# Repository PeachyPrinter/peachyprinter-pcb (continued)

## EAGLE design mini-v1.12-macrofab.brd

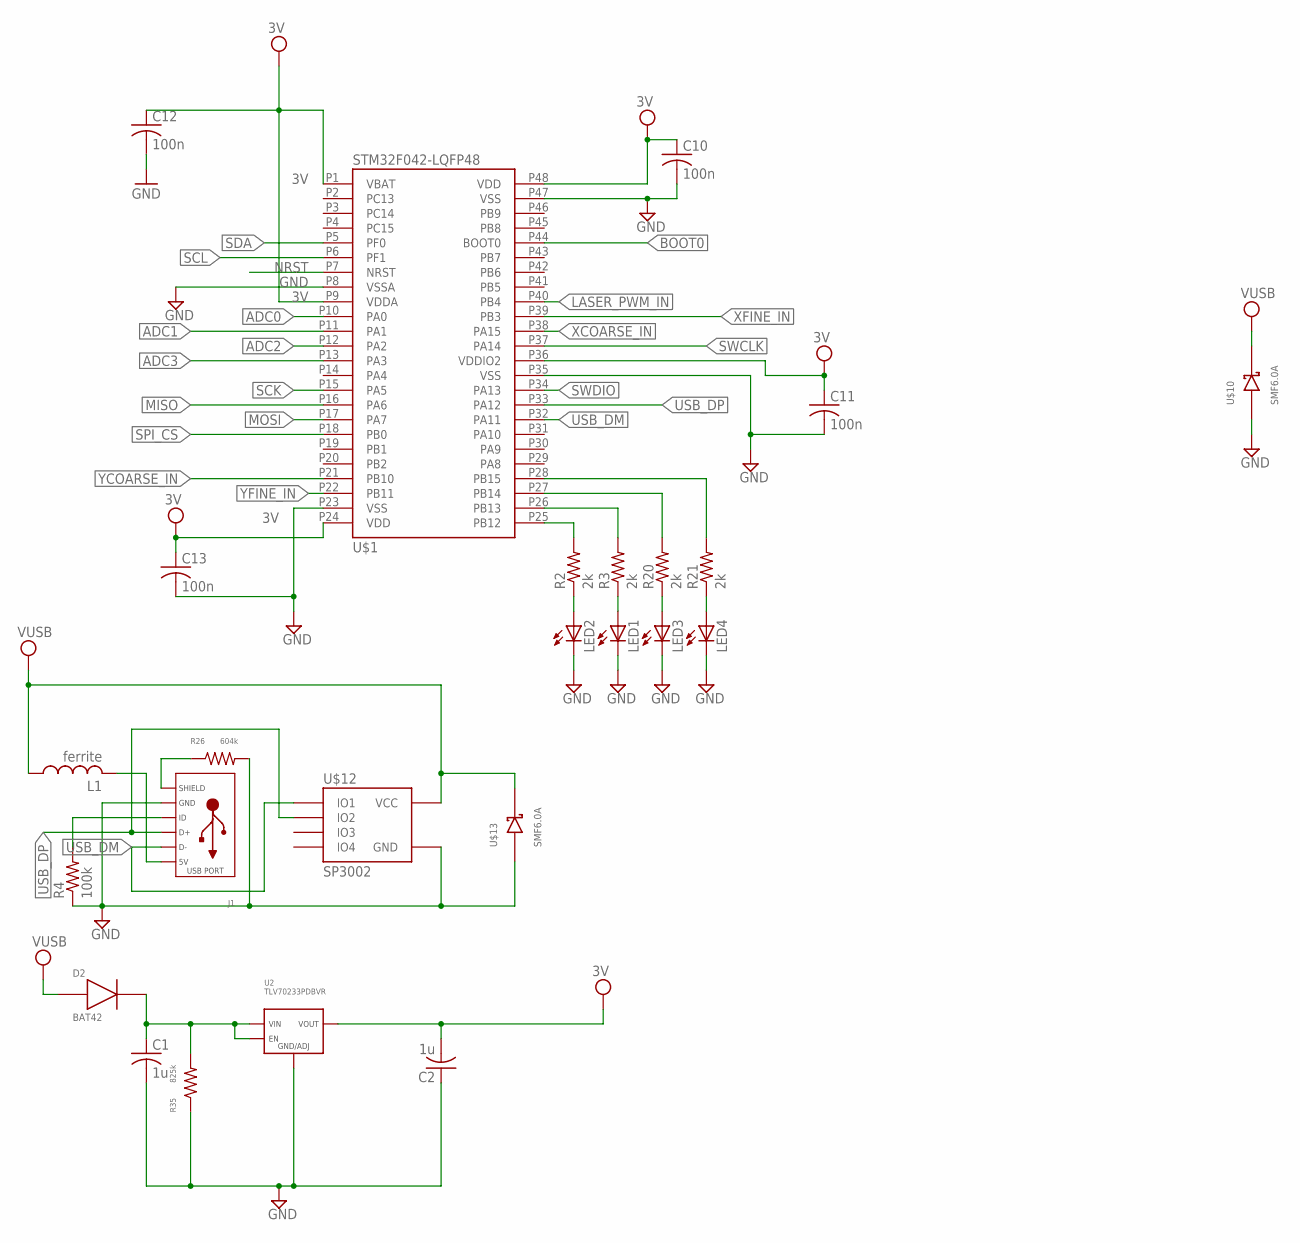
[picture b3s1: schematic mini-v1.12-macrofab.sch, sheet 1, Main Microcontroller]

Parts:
C1, C2: 1u; C0603
C10, C11, C12, C13: 100n; C0603
D2: BAT42; SOD323
J1: USB_MICRO_RIGHT; MICROUSB-RIGHT
L1: ferrite; C0603
LED1, LED2, LED3, LED4: LEDCHIP-LED0603; CHIP-LED0603
R2, R3, R20, R21: 2k; R0603
R4: 100k; R0603
R26: 604k; R0603
R35: 825k; R0603
U2: TLV70233PDBVR; SOT-23-5
U$1: STM32F042-LQFP48; LQFP48
U$10, U$13: SMF6.0A; SOD123
U$12: SP3002; SC70-6

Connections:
3V: C2.2, C10.1, C11.1, C12.1, C13.1, U2.P$5 (VOUT), U$1.P1 (VBAT), U$1.P9 (VDDA), U$1.P24 (VDD), U$1.P36 (VDDIO2), U$1.P48 (VDD); also elsewhere on the board
ADC0: U$1.P10 (PA0); also elsewhere on the board
ADC1: U$1.P11 (PA1); also elsewhere on the board
ADC2: U$1.P12 (PA2); also elsewhere on the board
ADC3: U$1.P13 (PA3); also elsewhere on the board
BOOT0: U$1.P44 (BOOT0); also elsewhere on the board
GND: C1.2, C2.1, C10.2, C11.2, C12.2, C13.2, J1.5 (GND), LED1.C, LED2.C, LED3.C, LED4.C, R4.1, R26.P$2, R35.P$1, U2.P$2 (GND/ADJ), U$1.P8 (VSSA), U$1.P23 (VSS), U$1.P35 (VSS), U$1.P47 (VSS), U$10.ANODE, U$12.P2 (GND), U$13.ANODE; also elsewhere on the board
LASER_PWM_IN: U$1.P40 (PB4); also elsewhere on the board
MISO: U$1.P16 (PA6); also elsewhere on the board
MOSI: U$1.P17 (PA7); also elsewhere on the board
unnamed: R2.2, U$1.P25 (PB12)
unnamed: LED2.A, R2.1
unnamed: C1.1, D2.1, R35.P$2, U2.P$1 (VIN), U2.P$3 (EN)
unnamed: J1.4 (ID), R4.2
unnamed: LED1.A, R3.1
unnamed: R3.2, U$1.P26 (PB13)
unnamed: J1.1 (5V), L1.2
unnamed: J1.S1 (SLD), J1.S2 (SLD), J1.S3 (SLD), J1.S4 (SLD), J1.S5 (SLD), J1.S6 (SLD), R26.P$1
unnamed: LED3.A, R20.1
unnamed: LED4.A, R21.1
unnamed: R20.2, U$1.P27 (PB14)
unnamed: R21.2, U$1.P28 (PB15)
NRST: U$1.P7 (NRST); also elsewhere on the board
SCK: U$1.P15 (PA5); also elsewhere on the board
SCL: U$1.P6 (PF1); also elsewhere on the board
SDA: U$1.P5 (PF0); also elsewhere on the board
SPI_CS: U$1.P18 (PB0); also elsewhere on the board
SWCLK: U$1.P37 (PA14); also elsewhere on the board
SWDIO: U$1.P34 (PA13); also elsewhere on the board
USB_DM: J1.2 (D-), U$1.P32 (PA11), U$12.P1 (IO1)
USB_DP: J1.3 (D+), U$1.P33 (PA12), U$12.P3 (IO2)
VUSB: D2.2, L1.1, U$10.CATHODE, U$12.P5 (VCC), U$13.CATHODE; also elsewhere on the board
XCOARSE_IN: U$1.P38 (PA15); also elsewhere on the board
XFINE_IN: U$1.P39 (PB3); also elsewhere on the board
YCOARSE_IN: U$1.P21 (PB10); also elsewhere on the board
YFINE_IN: U$1.P22 (PB11); also elsewhere on the board

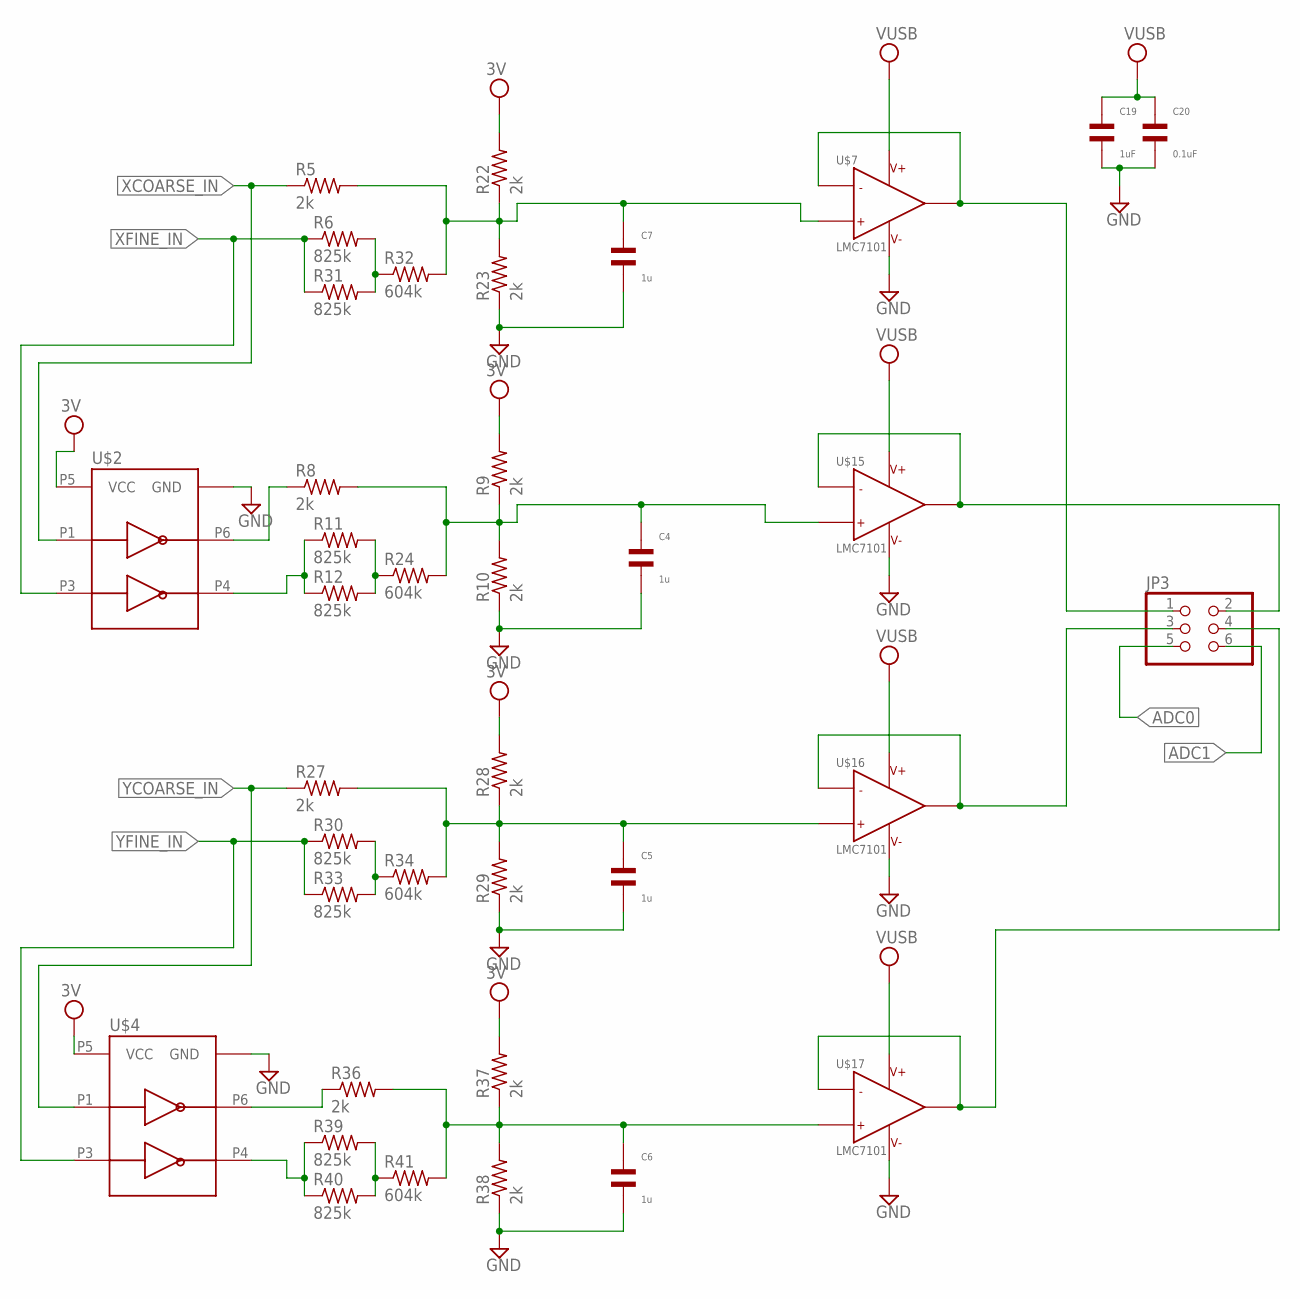
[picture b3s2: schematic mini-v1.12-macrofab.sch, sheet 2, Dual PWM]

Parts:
C4, C5, C6, C7: 1u; C0603
C19: 1uF; C0603
C20: 0.1uF; C0603
JP3: PINHD-2X3; 2X03
R5, R8, R9, R10, R22, R23, R27, R28, R29, R36, R37, R38: 2k; R0603
R6, R11, R12, R30, R31, R33, R39, R40: 825k; R0603
R24, R32, R34, R41: 604k; R0603
U$2, U$4: NC7WZ14P6X; SC70-6
U$7, U$15, U$16, U$17: LMC7101; SOT23-5

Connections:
3V: R9.2, R22.2, R28.2, R37.2, U$2.P5 (VCC), U$4.P5 (VCC); also elsewhere on the board
ADC0: JP3.5; also elsewhere on the board
ADC1: JP3.6; also elsewhere on the board
COARSE1: R8.1, U$2.P6 (Y1)
FINE1: R11.1, R12.1, U$2.P4 (Y2)
FINE3: R39.1, R40.1, U$4.P4 (Y2)
GND: C4.P$2, C5.P$2, C6.P$2, C7.P$2, C19.P$2, C20.P$2, R10.1, R23.1, R29.1, R38.1, U$2.P2 (GND), U$4.P2 (GND), U$7.5, U$15.5, U$16.5, U$17.5; also elsewhere on the board
unnamed: R36.1, U$4.P6 (Y1)
unnamed: R11.2, R12.2, R24.1
unnamed: C4.P$1, R8.2, R9.1, R10.2, R24.2, U$15.3
unnamed: R30.2, R33.2, R34.1
unnamed: R6.2, R31.2, R32.1
unnamed: C5.P$1, R27.2, R28.1, R29.2, R34.2, U$16.3
unnamed: R39.2, R40.2, R41.1
unnamed: C6.P$1, R36.2, R37.1, R38.2, R41.2, U$17.3
OUT: JP3.1, U$7.1, U$7.4
OUT1: JP3.2, U$15.1, U$15.4
OUT2: JP3.3, U$16.1, U$16.4
OUT3: JP3.4, U$17.1, U$17.4
VUSB: C19.P$1, C20.P$1, U$7.2, U$15.2, U$16.2, U$17.2; also elsewhere on the board
XCOARSE_IN: R5.1, U$2.P1 (A1); also elsewhere on the board
XFINE_IN: R6.1, R31.1, U$2.P3 (A2); also elsewhere on the board
XSUM: C7.P$1, R5.2, R22.1, R23.2, R32.2, U$7.3
YCOARSE_IN: R27.1, U$4.P1 (A1); also elsewhere on the board
YFINE_IN: R30.1, R33.1, U$4.P3 (A2); also elsewhere on the board

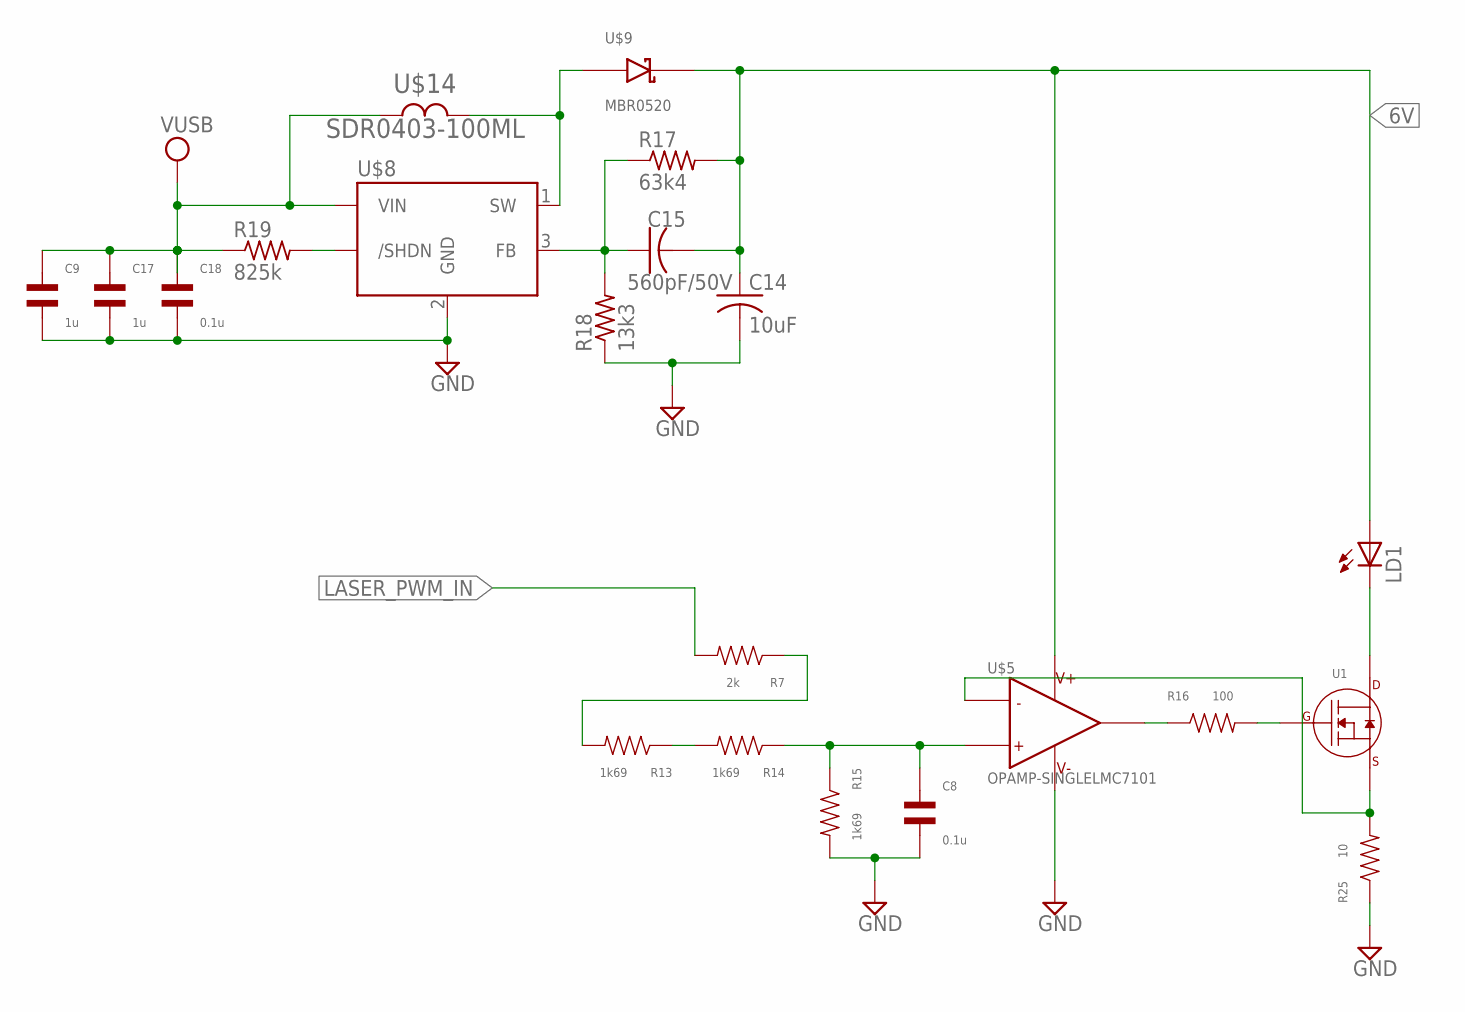
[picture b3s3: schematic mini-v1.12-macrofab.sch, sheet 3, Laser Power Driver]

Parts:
C8, C18: 0.1u; C0603
C9, C17: 1u; C0603
C14: 10uF; C0603
C15: 560pF/50V; C0603
LD1: LASERDIODELD2; LASERDIODE2; MPN 3 x (0552-2-15-15-11-27-10-0)
R7: 2k; R0603
R13, R14, R15: 1k69; R0603
R16: 100; R0603
R17: 63k4; R0603
R18: 13k3; R0603
R19: 825k; R0603
R25: 10; R0603
U1: N-CHANNEL_FET_SOT-23-3; SOT-23-3
U$5: OPAMP-SINGLELMC7101; SOT23-5
U$8: LMR62014; SOT23-5
U$9: MBR0520; SOD123
U$14: SDR0403-100ML; SDR0403

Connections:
6V: C14.1, C15.2, LD1.P$1 (A), R17.2, U$5.2 (V+), U$9.CATHODE
GND: C8.P$2, C9.P$2, C14.2, C17.P$2, C18.P$2, R15.P$2, R18.1, R25.P$1, U$5.5 (V-), U$8.2 (GND); also elsewhere on the board
LASER_PWM_IN: R7.P$2; also elsewhere on the board
unnamed: R7.P$1, R13.P$2
unnamed: R13.P$1, R14.P$2
unnamed: C8.P$1, R14.P$1, R15.P$1, U$5.3 (IN+)
unnamed: U$8.1 (SW), U$9.ANODE, U$14.P$2
unnamed: LD1.P$3 (C), U1.P$3 (DRAIN)
unnamed: R25.P$2, U1.P$2 (SOURCE), U$5.4 (IN-)
unnamed: R16.P$2, U1.P$1 (GATE)
unnamed: R16.P$1, U$5.1 (OUT)
unnamed: C15.1, R17.1, R18.2, U$8.3 (FB)
unnamed: R19.2, U$8.4 (/SHDN)
VUSB: C9.P$1, C17.P$1, C18.P$1, R19.1, U$8.5 (VIN), U$14.P$1; also elsewhere on the board

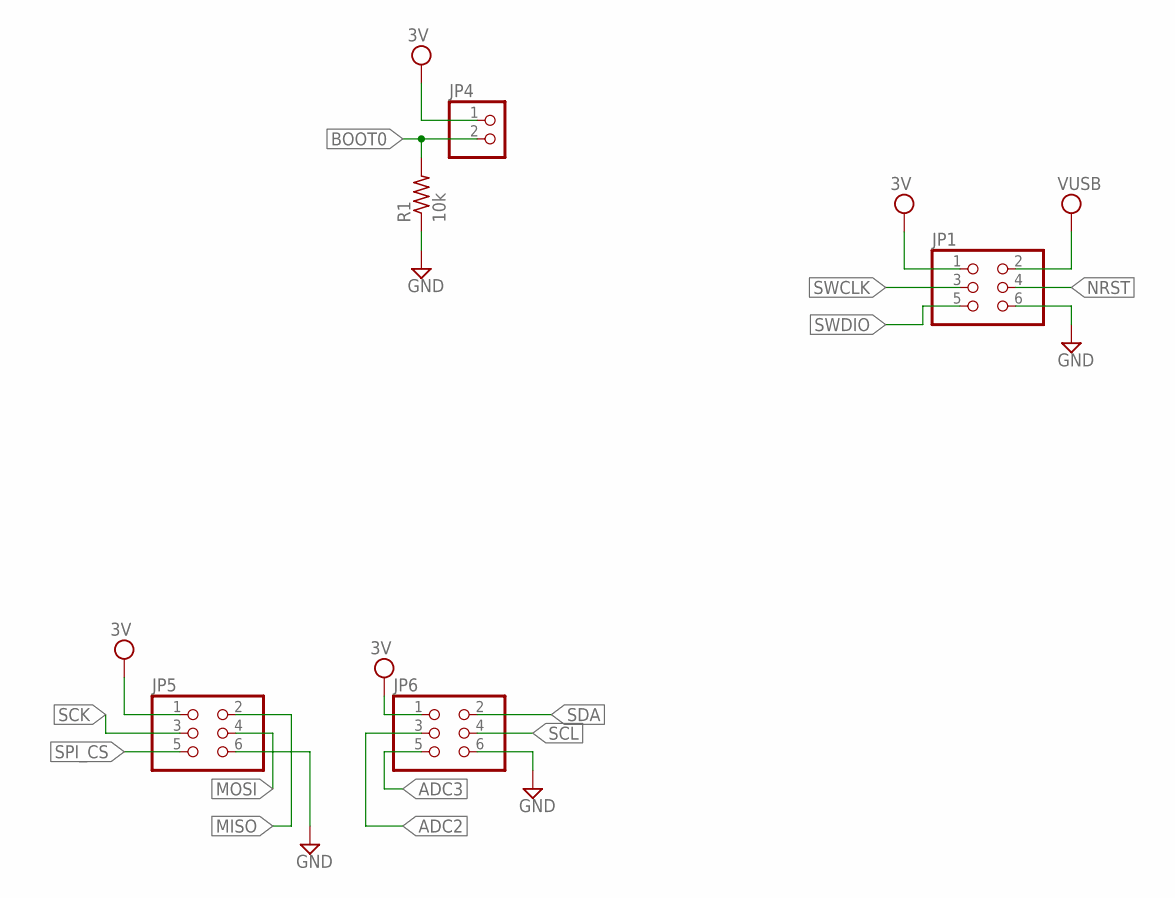
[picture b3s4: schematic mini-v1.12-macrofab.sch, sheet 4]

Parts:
JP1, JP5, JP6: PINHD-2X3; 2X03
JP4: PINHD-1X2; 1X02
R1: 10k; R0603

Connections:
3V: JP1.1, JP4.1, JP5.1, JP6.1; also elsewhere on the board
ADC2: JP6.3; also elsewhere on the board
ADC3: JP6.5; also elsewhere on the board
BOOT0: JP4.2, R1.2; also elsewhere on the board
GND: JP1.6, JP5.6, JP6.6, R1.1; also elsewhere on the board
MISO: JP5.2; also elsewhere on the board
MOSI: JP5.4; also elsewhere on the board
NRST: JP1.4; also elsewhere on the board
SCK: JP5.3; also elsewhere on the board
SCL: JP6.4; also elsewhere on the board
SDA: JP6.2; also elsewhere on the board
SPI_CS: JP5.5; also elsewhere on the board
SWCLK: JP1.3; also elsewhere on the board
SWDIO: JP1.5; also elsewhere on the board
VUSB: JP1.2; also elsewhere on the board

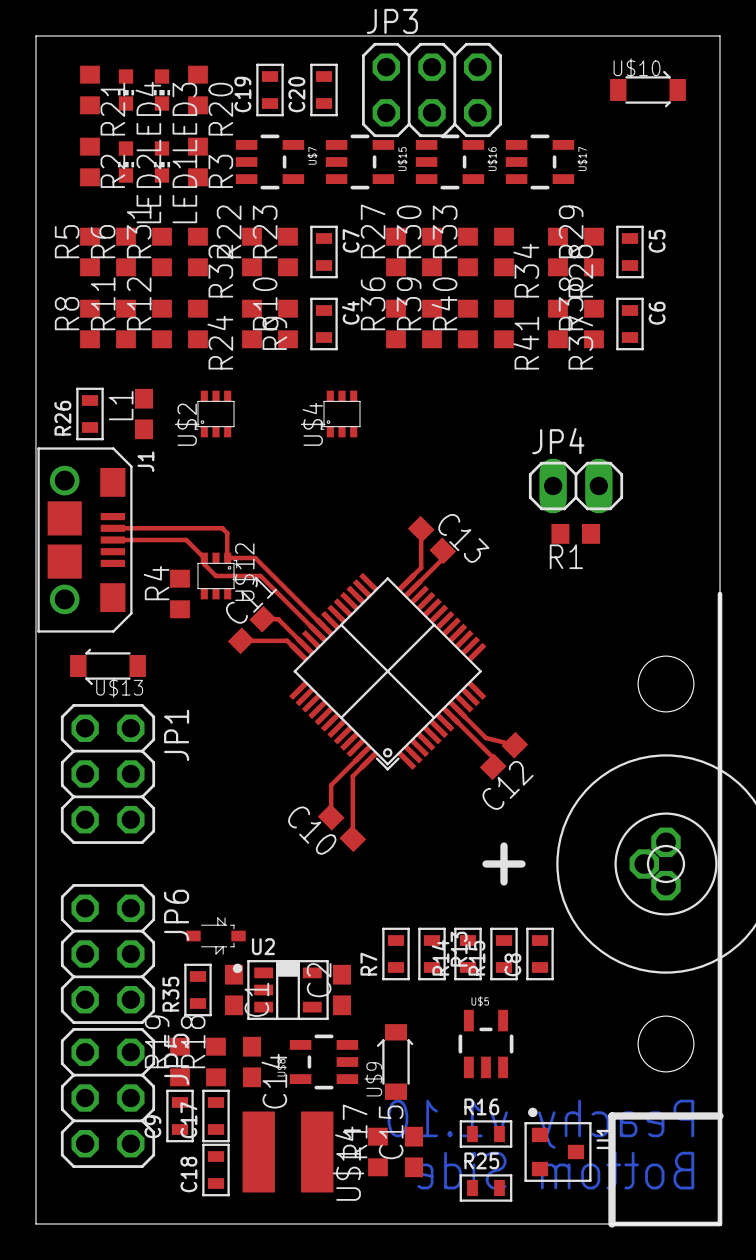
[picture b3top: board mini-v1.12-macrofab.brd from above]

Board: 2 copper layers, 38.0 x 66.0 mm, 88 parts (0 on the bottom side), 63 nets.

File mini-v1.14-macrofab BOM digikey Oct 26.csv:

Qty,Value,Device,DK P/N,Extended,DK for Ext$,Package,DK Order Oct 26,Boards Oct 26
13,100n,CAPACITOR_NP_0603,399-1095-2-ND,65000,362.7,C0603,4000,307
1,10uF,CAPACITOR_P_4MM,490-7201-2-ND,5000,484.35,CP4MM,250,250
5,1uF,C-USC0603,311-1443-2-ND,25000,178.25,C0603,4000,800
1,560pF/50V,C-USC0603,1276-1278-2-ND,5000,62.9,C0603,4000,4000
1,BAT42,DIODE_SOD-123,BAT42W-FDITR-ND,5000,442.2,SOD-123,120,120
4,,LEDCHIP-LED0603,475-2512-2-ND,20000,1071.2,CHIP-LED0603,1000,250
5,LMC7101,LMC7101,576-2575-2-ND,25000,7725.5,SOT23-5,600,120
1,LMR62014,LMR62014,296-39046-2-ND,5000,2595.55,SOT23-5,120,120
1,ferrite,L-US,,5000,,C0603,,0
1,MBR0520,MBR0520,MBR0520LT1GOSTR-ND,5000,397.2,SOD123,120,120
2,SMF6.0A,MBR0520,F5749TR-ND,10000,1517.1,SOD123,250,125
2,NC7WZ14P6X,NC7WZ14P6X,NC7WZ14P6XTR-ND,10000,810.4,SC70-6,250,125
2,BSS138,N-CHANNEL_FET_SOT-23-3,BSS138LT3GOSTR-ND,10000,451.64,SOT-23-3,240,120
3,,PINHD-2X3,952-1921-ND,15000,2617.5,2X03,360,120
2,10,RESISTOR_0603,311-10.0HRTR-ND,10000,21.26,R0603,5000,2500
1,100k,RESISTOR_0603,311-100KHRTR-ND,5000,9.62,R0603,5000,5000
2,13k3,RESISTOR_0603,311-13.3KHRTR-ND,10000,21.26,R0603,5000,2500
5,1k69,RESISTOR_0603,311-1.69KHRTR-ND,25000,47.5,R0603,5000,1000
16,2k,RESISTOR_0603,311-2.00KHRTR-ND,80000,139.2,R0603,5000,312
5,604k,RESISTOR_0603,311-604KHRTR-ND,25000,47.5,R0603,5000,1000
1,63k4,RESISTOR_0603,311-63.4KHRTR-ND,5000,12.45,R0603,5000,5000
10,825k,RESISTOR_0603,311-825KHRTR-ND,50000,21.62,R0603,5000,500
1,SDR0403-100ML,SDR0403,SDR0403-100MLTR-ND,5000,1287.25,SDR0403,120,120
1,SP3002-04JTG,SP3002,F2916TR-ND,5000,1824.75,SC70-6,120,120
1,STM32F070CBT6,STM32F042-LQFP48,497-15099-ND,5000,8179.93,LQFP48,120,120
1,TLV70233PDBVR,TLV70233PDBVR,296-39284-2-ND,5000,767.64,SOT-23-5,120,120
1,,USB_MICRO_RIGHT,609-4618-2-ND,5000,1258.45,MICROUSB-RIGHT,120,120
TOTAL,,,,,32354.92,,,
PER BOARD,,,,,6.470984,,,

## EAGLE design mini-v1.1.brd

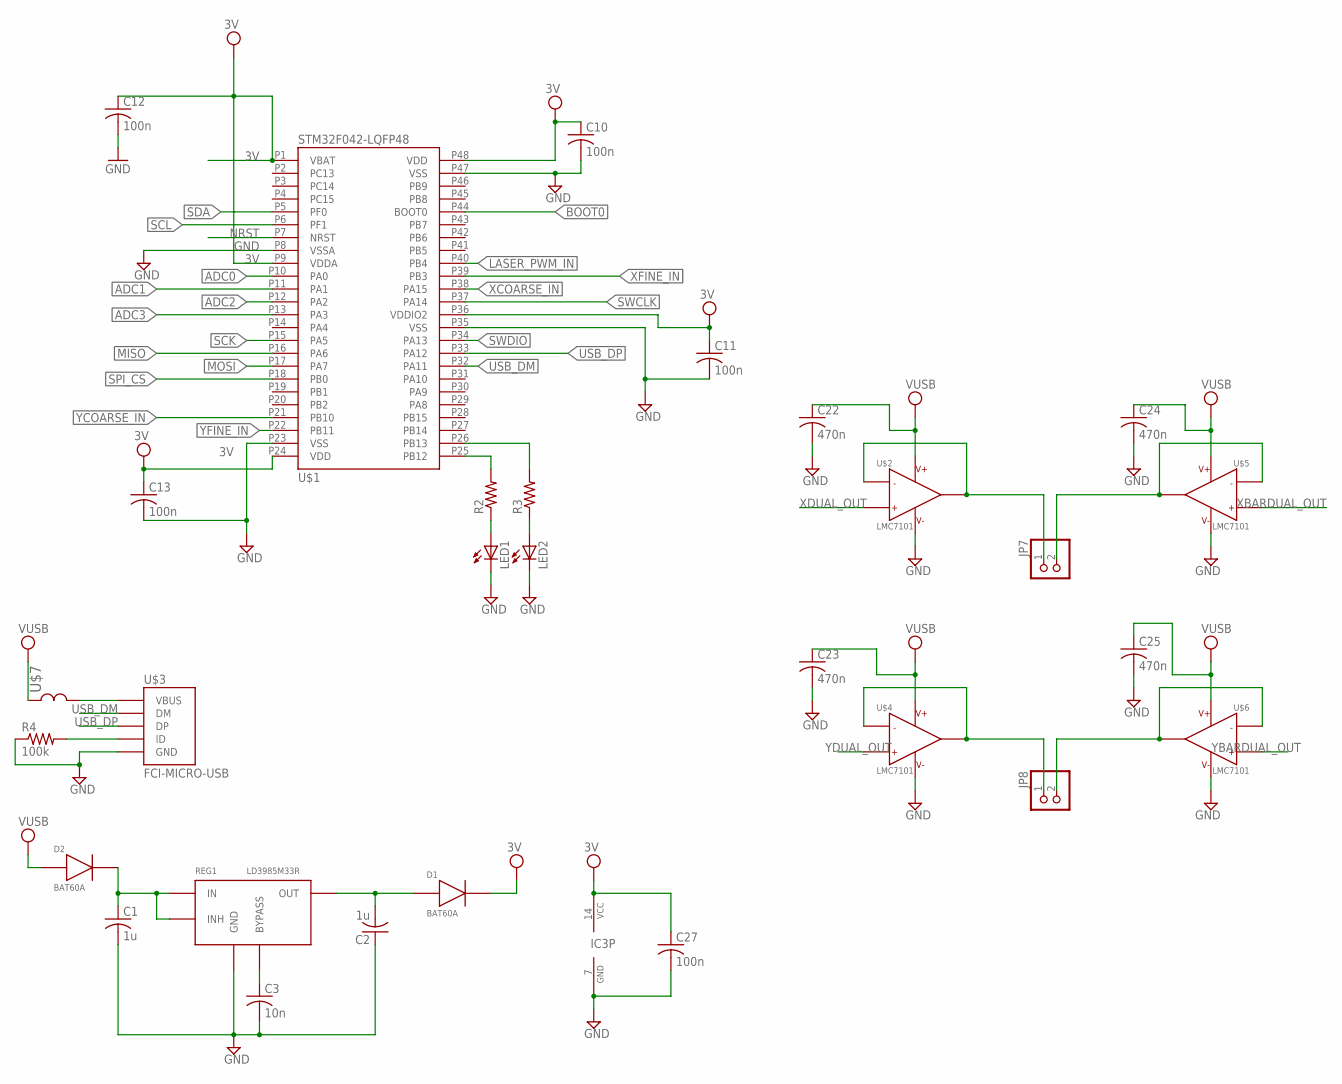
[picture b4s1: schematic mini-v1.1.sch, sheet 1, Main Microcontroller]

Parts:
C1, C2: 1u; C0603
C3: 10n; C0603
C10, C11, C12, C13, C27: 100n; C0603
C22, C23, C24, C25: 470n; C0603
D1, D2: BAT60A; SOD323
IC3: 74S04D; SO14
JP7, JP8: PINHD-1X2; 1X02
LED1, LED2: LED; SMARTLED-TTW
R2, R3: R-US_R0603; R0603
R4: 100k; R0603
REG1: LD3985M33R; SOT23-5L
U$1: STM32F042-LQFP48; LQFP48
U$2, U$4, U$5, U$6: LMC7101; SOT23-5
U$3: FCI-MICRO-USB; FCI-MICROUSB
U$7: L_TDK_1005; MLK1005

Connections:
3V: C10.1, C11.1, C12.1, C13.1, C27.1, D1.1, IC3.14 (VCC), U$1.P1 (VBAT), U$1.P9 (VDDA), U$1.P24 (VDD), U$1.P36 (VDDIO2), U$1.P48 (VDD); also elsewhere on the board
3V3: C2.2, D1.2, REG1.OUT
ADC0: U$1.P10 (PA0); also elsewhere on the board
ADC1: U$1.P11 (PA1); also elsewhere on the board
ADC2: U$1.P12 (PA2); also elsewhere on the board
ADC3: U$1.P13 (PA3); also elsewhere on the board
BOOT0: U$1.P44 (BOOT0); also elsewhere on the board
GND: C1.2, C2.1, C3.2, C10.2, C11.2, C12.2, C13.2, C22.2, C23.2, C24.2, C25.2, C27.2, IC3.7 (GND), LED1.C@1 (C), LED2.C@1 (C), R4.1, REG1.GND, U$1.P8 (VSSA), U$1.P23 (VSS), U$1.P35 (VSS), U$1.P47 (VSS), U$2.5, U$3.P5 (GND), U$4.5, U$5.5, U$6.5; also elsewhere on the board
LASER_PWM_IN: U$1.P40 (PB4); also elsewhere on the board
MISO: U$1.P16 (PA6); also elsewhere on the board
MOSI: U$1.P17 (PA7); also elsewhere on the board
unnamed: C3.1, REG1.BYPASS
unnamed: R2.2, U$1.P25 (PB12)
unnamed: LED1.A@1 (A), R2.1
unnamed: C1.1, D2.1, REG1.IN, REG1.INHIBIT (INH)
unnamed: R4.2, U$3.P4 (ID)
unnamed: JP7.1, U$2.1, U$2.4
unnamed: JP8.1, U$4.1, U$4.4
unnamed: LED2.A@1 (A), R3.1
unnamed: R3.2, U$1.P26 (PB13)
unnamed: U$3.P1 (VBUS), U$7.P$2
unnamed: JP7.2, U$5.1, U$5.4
unnamed: JP8.2, U$6.1, U$6.4
NRST: U$1.P7 (NRST); also elsewhere on the board
SCK: U$1.P15 (PA5); also elsewhere on the board
SCL: U$1.P6 (PF1); also elsewhere on the board
SDA: U$1.P5 (PF0); also elsewhere on the board
SPI_CS: U$1.P18 (PB0); also elsewhere on the board
SWCLK: U$1.P37 (PA14); also elsewhere on the board
SWDIO: U$1.P34 (PA13); also elsewhere on the board
USB_DM: U$1.P32 (PA11), U$3.P2 (DM)
USB_DP: U$1.P33 (PA12), U$3.P3 (DP)
VUSB: C22.1, C23.1, C24.1, C25.1, D2.2, U$2.2, U$4.2, U$5.2, U$6.2, U$7.P$1; also elsewhere on the board
XBARDUAL_OUT: U$5.3; also elsewhere on the board
XCOARSE_IN: U$1.P38 (PA15); also elsewhere on the board
XDUAL_OUT: U$2.3; also elsewhere on the board
XFINE_IN: U$1.P39 (PB3); also elsewhere on the board
YBARDUAL_OUT: U$6.3; also elsewhere on the board
YCOARSE_IN: U$1.P21 (PB10); also elsewhere on the board
YDUAL_OUT: U$4.3; also elsewhere on the board
YFINE_IN: U$1.P22 (PB11); also elsewhere on the board

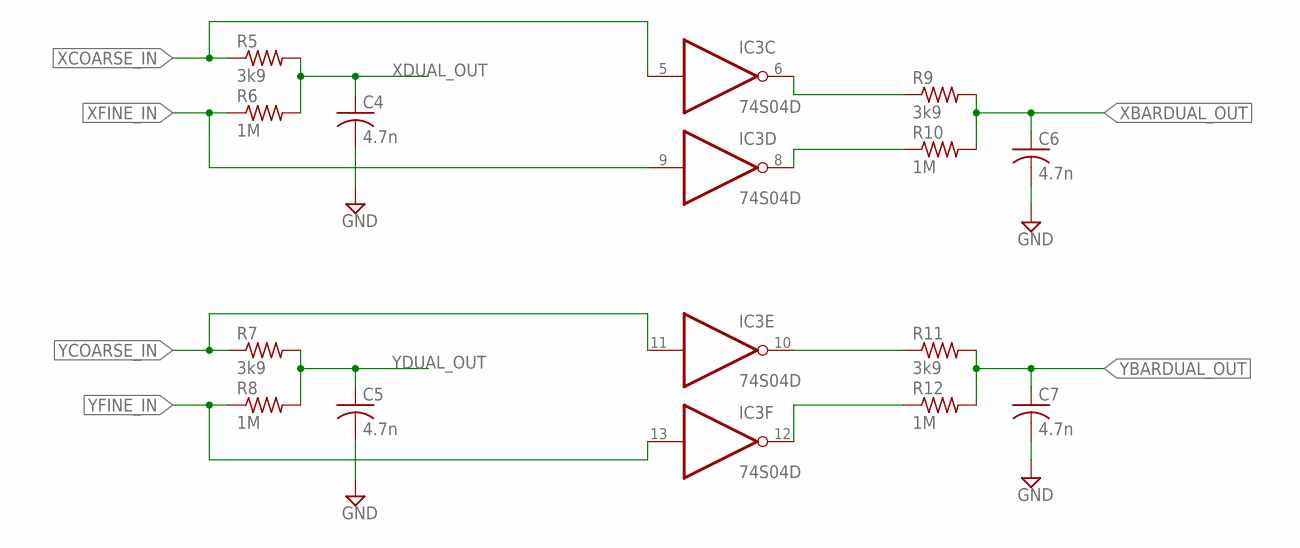
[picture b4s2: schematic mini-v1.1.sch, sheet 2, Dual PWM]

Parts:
C4, C5, C6, C7: 4.7n; C0603
IC3: 74S04D; SO14
R5, R7, R9, R11: 3k9; R0603
R6, R8, R10, R12: 1M; R0603

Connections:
GND: C4.2, C5.2, C6.2, C7.2; also elsewhere on the board
unnamed: IC3.10 (O), R11.1
unnamed: IC3.12 (O), R12.1
unnamed: IC3.8 (O), R10.1
unnamed: IC3.6 (O), R9.1
XBARDUAL_OUT: C6.1, R9.2, R10.2; also elsewhere on the board
XCOARSE_IN: IC3.5 (I), R5.1; also elsewhere on the board
XDUAL_OUT: C4.1, R5.2, R6.2; also elsewhere on the board
XFINE_IN: IC3.9 (I), R6.1; also elsewhere on the board
YBARDUAL_OUT: C7.1, R11.2, R12.2; also elsewhere on the board
YCOARSE_IN: IC3.11 (I), R7.1; also elsewhere on the board
YDUAL_OUT: C5.1, R7.2, R8.2; also elsewhere on the board
YFINE_IN: IC3.13 (I), R8.1; also elsewhere on the board

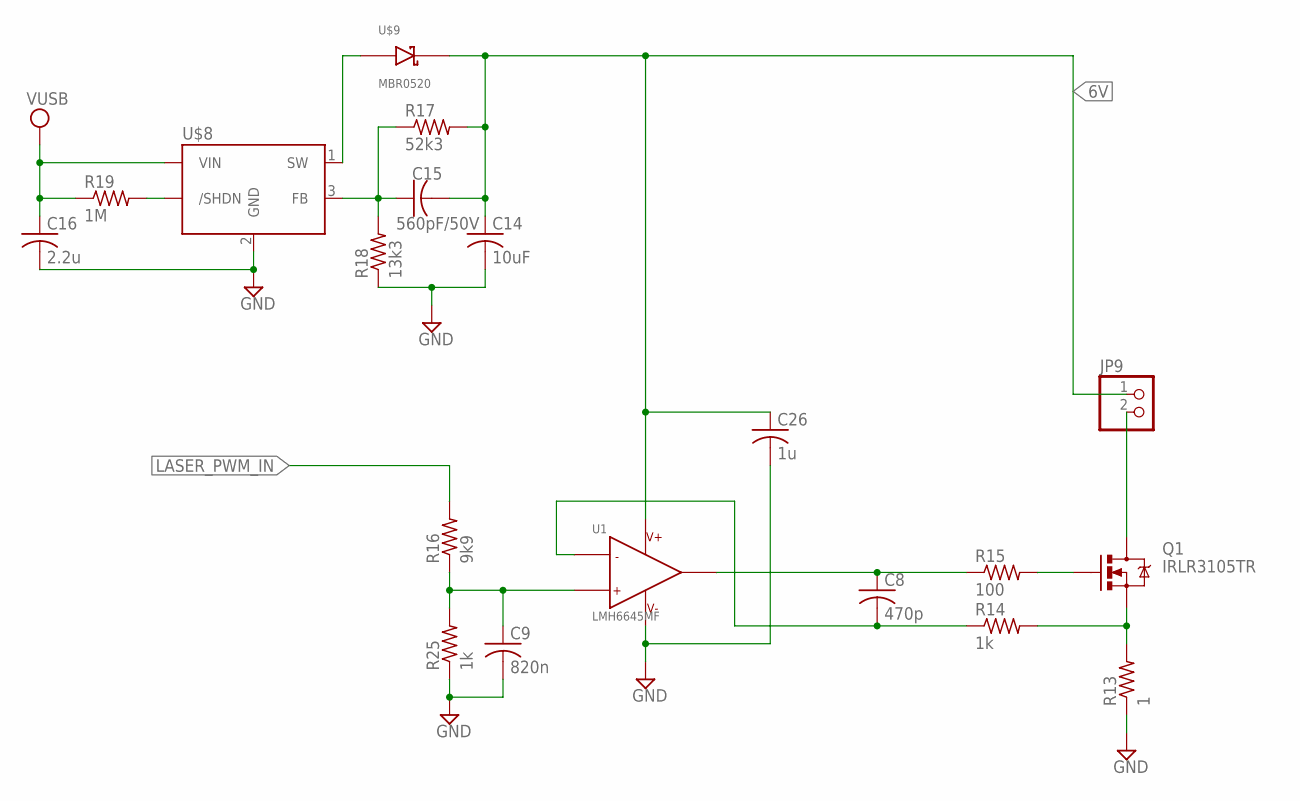
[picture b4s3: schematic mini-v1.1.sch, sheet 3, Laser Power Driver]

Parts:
C8: 470p; C0603
C9: 820n; C0603
C14: 10uF; C0603
C15: 560pF/50V; C0603
C16: 2.2u; C0603
C26: 1u; C0603
JP9: PINHD-1X2; 1X02
Q1: IRLR3105TR; DPAK
R13: 1; R0603
R14, R25: 1k; R0603
R15: 100; R0603
R16: 9k9; R0603
R17: 52k3; R0603
R18: 13k3; R0603
R19: 1M; R0603
U1: LMH6645MF; SOT23-5
U$8: LMR62014; SOT23-5
U$9: MBR0520; SOD123

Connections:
6V: C14.1, C15.2, C26.1, JP9.1, R17.2, U1.5 (V+), U$9.CATHODE
GND: C9.2, C14.2, C16.2, C26.2, R13.1, R18.1, R25.1, U1.2 (V-), U$8.2 (GND); also elsewhere on the board
LASER_PWM_IN: R16.2; also elsewhere on the board
unnamed: U$8.1 (SW), U$9.ANODE
unnamed: JP9.2, Q1.4 (D)
unnamed: Q1.3 (S), R13.2, R14.2
unnamed: C8.2, R14.1, U1.4 (IN-)
unnamed: Q1.1 (G), R15.2
unnamed: C8.1, R15.1, U1.1 (OUT)
unnamed: C9.1, R16.1, R25.2, U1.3 (IN+)
unnamed: C15.1, R17.1, R18.2, U$8.3 (FB)
unnamed: R19.2, U$8.4 (/SHDN)
VUSB: C16.1, R19.1, U$8.5 (VIN); also elsewhere on the board

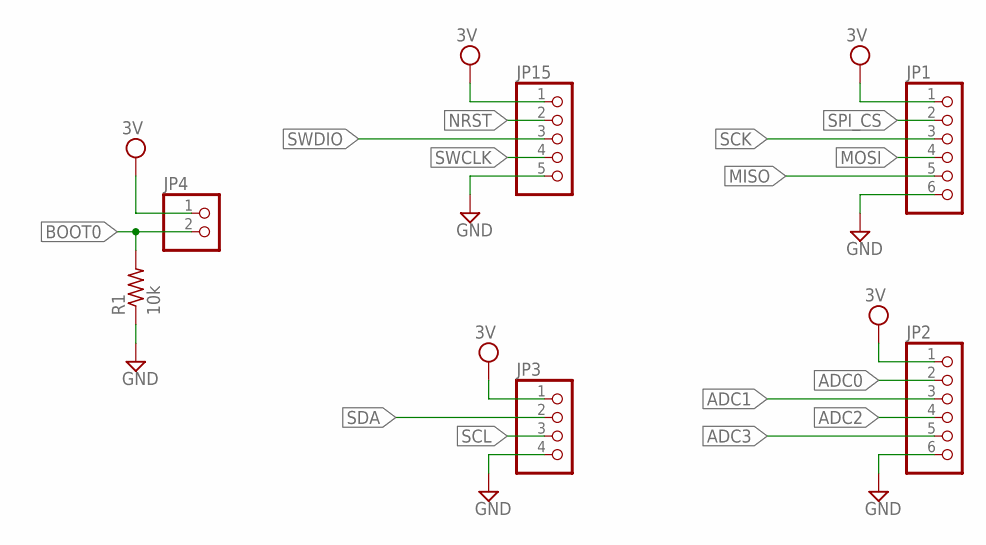
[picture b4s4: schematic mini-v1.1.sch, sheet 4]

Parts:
JP1, JP2: PINHD-1X6; 1X06
JP3: PINHD-1X4; 1X04
JP4: PINHD-1X2; 1X02
JP15: PINHD-1X5; 1X05
R1: 10k; R0603

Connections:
3V: JP1.1, JP2.1, JP3.1, JP4.1, JP15.1; also elsewhere on the board
ADC0: JP2.2; also elsewhere on the board
ADC1: JP2.3; also elsewhere on the board
ADC2: JP2.4; also elsewhere on the board
ADC3: JP2.5; also elsewhere on the board
BOOT0: JP4.2, R1.2; also elsewhere on the board
GND: JP1.6, JP2.6, JP3.4, JP15.5, R1.1; also elsewhere on the board
MISO: JP1.5; also elsewhere on the board
MOSI: JP1.4; also elsewhere on the board
NRST: JP15.2; also elsewhere on the board
SCK: JP1.3; also elsewhere on the board
SCL: JP3.3; also elsewhere on the board
SDA: JP3.2; also elsewhere on the board
SPI_CS: JP1.2; also elsewhere on the board
SWCLK: JP15.4; also elsewhere on the board
SWDIO: JP15.3; also elsewhere on the board

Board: 2 copper layers, 67 parts (0 on the bottom side), 55 nets, no tracks yet.
